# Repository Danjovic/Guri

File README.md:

# Guri
Ignition controller for VW air cooled engines.

Volkswagen air cooled engines have been produced over 70 years and millions of them still in use today pushing beetles, buses and even small aircraft. Such engines cheap and easy to maintain yet their outdated design provides space for a lot of hacking. 

The present project addresses a small but important improvement in the engine by the control of coil charging time and providing constant time for burning the fuel mixture allover the engine RPM range.

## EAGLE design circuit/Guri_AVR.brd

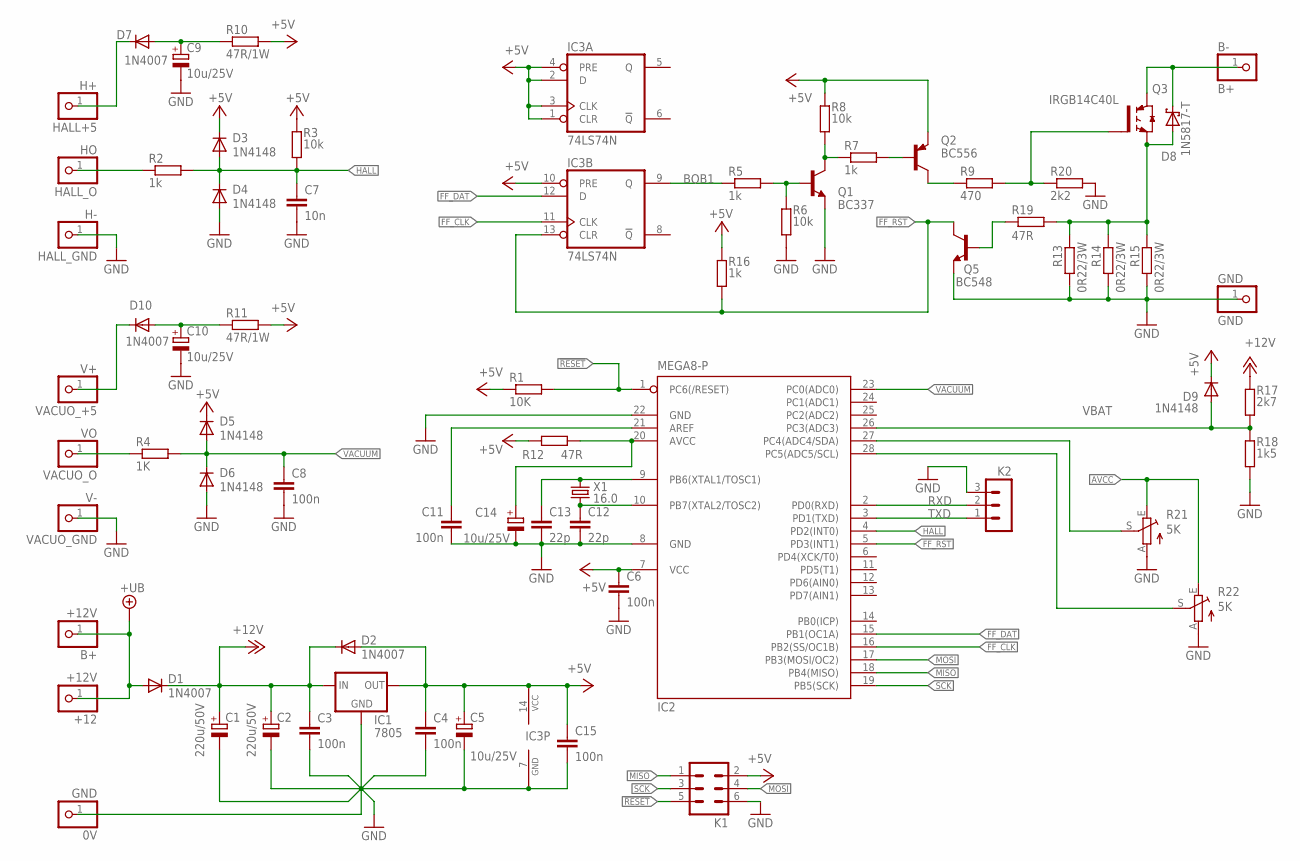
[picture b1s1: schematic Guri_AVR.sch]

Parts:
0V: GND; 1X01
+12: +12V; 1X01
B+: +12V; 1X01
B-: B+; 1X01
C1, C2: 220u/50V; E5-10,5
C3, C4, C6, C8, C11, C15: 100n; C050-025X075
C5, C9, C10, C14: 10u/25V; E2-5
C7: 10n; C050-025X075
C12, C13: 22p; C050-024X044
D1, D2, D7, D10: 1N4007; D-7.5
D3, D4, D5, D6, D9: 1N4148; DO35-7
D8: 1N5817-T; DO41-7.6
GND: GND; 1X01
H+: HALL+5; 1X01
H-: HALL_GND; 1X01
HO: HALL_O; 1X01
IC1: 7805; 78XXS
IC2: MEGA8-P; DIL28-3
IC3: 74LS74N; DIL14
K1: ML6
K2: MA03-1
Q1: BC337; TO92-EBC
Q2: BC556; TO92-EBC
Q3: IRGB14C40L; TO262-V
Q5: BC548; TO92-EBC
R1: 10K; 0207/7L
R2, R5, R7, R16: 1k; 0207/7L
R3, R6, R8: 10k; 0207/7L
R4: 1K; 0207/7L
R9: 470; 0207/7L
R10, R11: 47R/1W; 0207/7L
R12, R19: 47R; 0207/7L
R13, R14, R15: 0R22/3W; 0309/10
R17: 2k7; 0207/7L
R18: 1k5; 0207/7L
R20: 2k2; 0207/7L
R21, R22: 5K; ECP10P
V+: VACUO_+5; 1X01
V-: VACUO_GND; 1X01
VO: VACUO_O; 1X01
X1: 16.0; HC49/S

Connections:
!RESET: IC2.1 (PC6(/RESET)), K1.5, R1.4 (2)
+5V: C4.1, C5.+, C6.1, C15.1, D2.A, D3.C, D5.C, D9.C, IC1.OUT, IC2.7 (VCC), IC3.1 (CLR), IC3.2 (D), IC3.3 (CLK), IC3.4 (PRE), IC3.10 (PRE), IC3.14 (VCC), K1.2, Q2.E, R1.3 (1), R3.4 (2), R8.4 (2), R10.4 (2), R11.4 (2), R12.4 (2), R16.4 (2)
+12V: C1.+, C2.+, C3.1, D1.C, D2.C, IC1.IN, R17.3 (1)
+UB: +12.1, B+.1, D1.A
AREF: C11.1, IC2.21 (AREF)
AVCC: C14.+, IC2.20 (AVCC), R12.3 (1), R21.E, R22.E
BOB1: IC3.9 (Q), R5.3 (1)
FF_CLK: IC2.16 (PB2(SS/OC1B)), IC3.11 (CLK)
FF_DAT: IC2.15 (PB1(OC1A)), IC3.12 (D)
FF_RST: IC2.5 (PD3(INT1)), IC3.13 (CLR), Q5.C, R16.3 (1)
GND: 0V.1, C1.-, C2.-, C3.2, C4.2, C5.-, C6.2, C7.2, C8.2, C9.-, C10.-, C11.2, C12.2, C13.2, C14.-, C15.2, D4.A, D6.A, GND.1, H-.1, IC1.GND, IC2.8 (GND), IC2.22 (GND), IC3.7 (GND), K1.6, K2.3, Q1.E, Q5.E, R6.3 (1), R13.1, R14.1, R15.1, R18.4 (2), R20.4 (2), R21.A, R22.A, V-.1
HALL: C7.1, D3.A, D4.C, IC2.4 (PD2(INT0)), R2.4 (2), R3.3 (1)
HALL_IN: HO.1, R2.3 (1)
MISO: IC2.18 (PB4(MISO)), K1.1
MOSI: IC2.17 (PB3(MOSI/OC2)), K1.4
unnamed: C9.+, D7.A, R10.3 (1)
unnamed: D10.C, V+.1
unnamed: Q2.B, R7.4 (2)
unnamed: Q1.C, R7.3 (1), R8.3 (1)
unnamed: Q1.B, R5.4 (2), R6.4 (2)
unnamed: C10.+, D10.A, R11.3 (1)
unnamed: D7.C, H+.1
unnamed: Q2.C, R9.3 (1)
unnamed: Q3.1 (G), R9.4 (2), R20.3 (1)
unnamed: B-.1, D8.C, Q3.2 (C)
unnamed: C13.1, IC2.9 (PB6(XTAL1/TOSC1)), X1.2
unnamed: C12.1, IC2.10 (PB7(XTAL2/TOSC2)), X1.1
unnamed: Q5.B, R19.4 (2)
unnamed: IC2.27 (PC4(ADC4/SDA)), R21.S
unnamed: IC2.28 (PC5(ADC5/SCL)), R22.S
unnamed: D8.A, Q3.3 (E), R13.2, R14.2, R15.2, R19.3 (1)
RXD: IC2.2 (PD0(RXD)), K2.2
SCK: IC2.19 (PB5(SCK)), K1.3
TXD: IC2.3 (PD1(TXD)), K2.1
VAC-IN: R4.3 (1), VO.1
VACUUM: C8.1, D5.A, D6.C, IC2.23 (PC0(ADC0)), R4.4 (2)
VBAT: D9.A, IC2.26 (PC3(ADC3)), R17.4 (2), R18.3 (1)

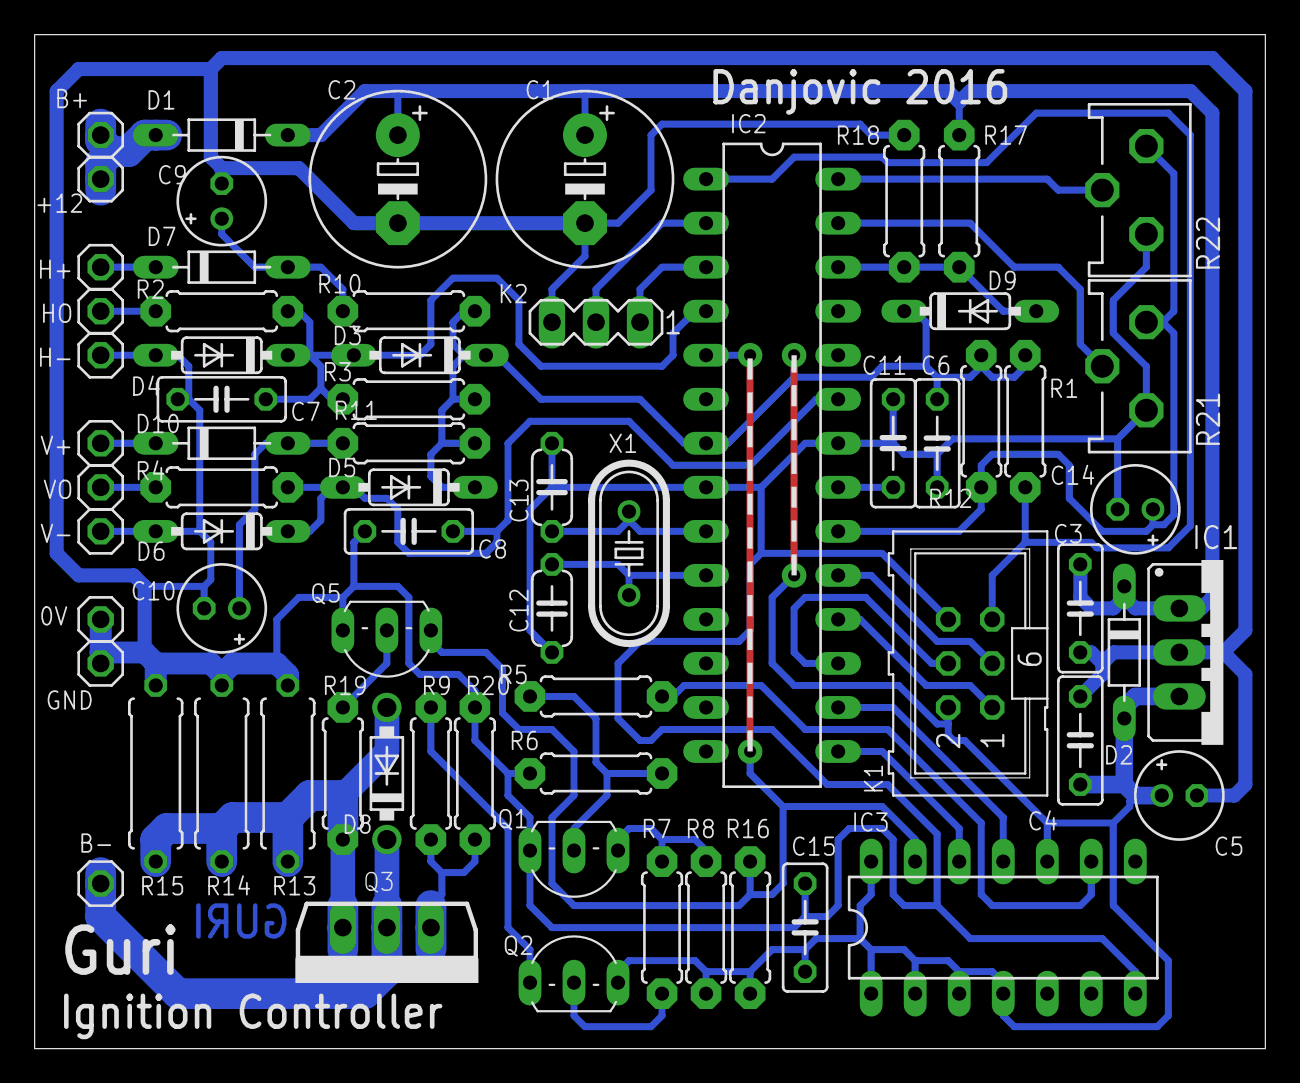
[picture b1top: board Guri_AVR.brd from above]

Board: 2 copper layers, 71.0 x 58.5 mm, 68 parts (0 on the bottom side), 37 nets.

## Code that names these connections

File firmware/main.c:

/*
   Guri: Ignition Timing Controller for VW Air Cooled engines
   
   Danjovic 2016 - Danjovic@hotmail.com
 

                    ATMega8
                   +---_---+  
        nRESET/PC6-|1    28|- PC5/ADC5/SCL - POT2
   DEBUG - RXD/PD0-|2    27|- PC4/ADC4/SDA - POT1
   DEBUG - TXD/PD1-|3    26|- PC3/ADC3 - VBAT
 IGNTSTS -INT0/PD2-|4    25|- PC2/ADC2
 OVERCUR  INT1/PD3-|5    24|- PC1/ADC1
        XCK\T0/PD4-|6    23|- PC0/ADC0 - VACUUM
               VCC-|7    22|- GND 
               GND-|8    21|- AREF
           XT1/PB6-|9    20|- AVCC
           XT2/PB7-|10   19|- PB5/SCK
            T1/PD5-|11   18|- PB4/MISO
          AIN0/PD6-|12   17|- PB3/MOSI/OC2
          AIN1/PD7-|13   16|- PB2/nSS/OC1B - FF_CLK
          ICP1/PB0-|14   15|- PB1/OC1A - FF_DAT
                   +-------+
   
*/

#define DEBUG

// *******************************Libraries************************
#include <avr/io.h>
#include <avr/pgmspace.h>
#include <avr/interrupt.h>
#include <inttypes.h>
#include <util/delay.h>
#include <avr/wdt.h> 

#ifdef DEBUG
#include <stdio.h>
#include "uart.h"
#include "uart.c"

#endif
// *******************************Definitions**********************
#define FF_CLK (1<<PB2)
#define FF_DAT (1<<PB1)

//


//F_CPU 12000000

#define TIME_FACTOR 64000000UL/F_CPU  // us
#define RPM_FACTOR  7500000UL
#define MIN_RPM      150
#define MAX_RPM     6200

#define _t_max_rpm  RPM_FACTOR/MAX_RPM     
#define _t_min_rpm  62500    //  120 RPM
#define _t_base     2000 / TIME_FACTOR // 2ms
#define _t_burn     500 / TIME_FACTOR  // 0,5ms 

#define _v_8V       114   // ADC reading for 8Volts
#define _v_15V      214   // ADC reading for 15Volts
#define _delta_Vbat ( _v_15V - _v_8V ) // delta


#define _v_127mmHg       114   // ADC reading for 127.5 mmHg
#define _v_270mmHg      214   // ADC reading for 270 mmHg
#define _delta_Vacuum ( _v_270mmHg - _v_127mmHg ) // delta


#define _v_factor      8    // Multiply factor to reduce loss of bits
                         // in the interpolation
#define _v_interval    15   // ending interval 


// *******************************Variables************************
static volatile uint8_t Vbat=0;
static volatile uint8_t Vacuum=0;


const uint16_t PROGMEM Tcharge[16] = { 600,575,550,525,500,475,450,425,400,375,350,325,300,275,250,225 };
const uint16_t PROGMEM Tvacuum[16] = {   0, 25, 50, 75,100,125,150,175,200,225,250,275,300,325,350,375 };
//const uint16_t PROGMEM constants[] = {_t_max_rpm, _t_min_rpm, _t_base, _t_burn } ;

// *******************************Function Prototypes**************
void init_hw(void);
uint16_t read_adc(uint8_t channel);


// *******************************Main Loop************************
int main (void) {

	uint8_t v;
	uint16_t temp16;

	init_hw();      // Initialize hardware
	                // Initialize variables
#ifdef DEBUG
	uart_init();    // Initialize USART, 19200 8N1
    stdout = &uart_output;
    stdin  = &uart_input;
	printf_P(PSTR("Guri:Debug mode\n"));
			   
#endif			   


    while(1) {
        puts("Press a Key");
        v = getchar();
		temp16=read_adc(0); printf("vacuum: %u\n",temp16);  
		temp16=read_adc(3); printf("vbat  : %u\n",temp16);  
		temp16=read_adc(4); printf("pot1  : %u\n",temp16);  
		temp16=read_adc(5); printf("pot2  : %u\n",temp16); 
 		
    }
		   
		   
			   
	//sei();     // start interrupts
	
	wdt_reset();
	wdt_disable();
	wdt_enable(WDTO_500MS);
	
	for (;;) {
		// reset watchdog
		wdt_reset();
		
		// read Vbat
		ADCSRA &= ~7; // select channel 0 (VBAT)
		ADCSRA |= ADSC; // start conversion
		while  	bit_is_set(ADCSRA, ADSC); // wait end of conversion
		v = ADCH; // read Battery voltage
		if (v < _v_8V ) v  =  _v_8V;  // low value limit
		if (v > _v_15V ) v = _v_15V;  // high value limit
		// convert value into index to lookup table		
		temp16 = (v - _v_8V) * ( _v_factor * _v_interval);
		temp16 = temp16 / (_v_factor * _delta_Vbat);
		v = (uint8_t)temp16;
		Vbat = v;
		
	
		// read Vaccum sensor
		ADCSRA |= 1; // select channel 1 (VACUUM)
		ADCSRA |= ADSC; // start conversion
		while  	bit_is_set(ADCSRA, ADSC); // wait end of conversion
		v = ADCH; // read vacuum at Manifold	
		if (v < _v_127mmHg ) v  =  _v_127mmHg;  // low value limit
		if (v > _v_270mmHg ) v = _v_270mmHg;  // high value limit
		// convert value into index to lookup table
		temp16 = (v - _v_127mmHg) * ( _v_factor * _v_interval);
		temp16 = temp16 / (_v_factor * _delta_Vacuum);
		v = (uint8_t)temp16;		
		Vacuum = v;
		
	}

}

// ******************************Initialize Hardware***************
void init_hw(void){
	
	// Initialize I/O
	DDRB = (FF_CLK | FF_DAT);
	PORTB = 0;
	PORTB |= FF_CLK;  // pulse clock to turn off coil 
	PORTB = 0;
	
	// Initialize ADC
	ADMUX =  (1<<REFS0); // Aref=AVcc
	ADCSRA=(1<<ADEN)|(1<<ADPS2)|(1<<ADPS1)|(1<<ADPS0); //Prescalar div factor =128
  
	
	// Initialize Timer
	TCCR1A=0;          // Timer 1 in Normal mode, OC1A/B disconnected
	TCNT1  = 0;        // Clear Timer1
	TCCR1B=(3<CS10);   // Prescaler 64, overflow 262ms
	
	// Initialize Interrupts
	TIMSK = (1<<TOIE1) + (1<<OCIE1A) + (1<<OCIE1B) ;// Overflow, compare A and B
	MCUCR = (3<<ISC01);// INT0 on rising edge
	GICR  = (1<<INT0); // INT0  
	//sei();
}

// ******************************Perform one Analog reading********
uint16_t read_adc(uint8_t channel) {
		ADMUX &= ~7;     //clear 3 lsb from channel selection
		ADMUX |= ( channel & 7); // range check in argument
		ADCSRA |= (1<<ADSC); // start conversion
		while  	bit_is_set(ADCSRA, ADSC); // wait end of conversion
		return ADC; // read Battery voltage, 8 bits
}

// ******************************Timer 1 Overflow******************
ISR (TIMER1_OVF_vect) {
	
	PORTB &= ~FF_DAT;   // Turn off coil and timers
	asm ("nop");		
	PORTB |= FF_CLK;
	asm ("nop");
	PORTB &= ~FF_CLK;
	
	TCCR1B = 0;           // Stop Timer1
	TCNT1  = 0;           // Clear Timer1
	
	TIMSK = (1<<TOIE1);	// Disable compare interrupts
}

// ******************************Timer 1 Compare A*****************
ISR (TIMER1_COMPA_vect) {     // Start Charging the Coil 
	PORTB |= FF_DAT;
	asm ("nop");	
	PORTB |= FF_CLK;
	asm ("nop");
	PORTB &= ~FF_CLK;
}

// ******************************Timer 1 Compare B*****************
ISR (TIMER1_COMPB_vect) {     // Stop Charge, generate Spark
	PORTB &= ~FF_DAT;
	asm ("nop");	
	PORTB |= FF_CLK;
	asm ("nop");
	PORTB &= ~FF_CLK;
}

// ******************************External Interrupt****************
ISR (INT0_vect) {             // Measure Tcycle
	uint16_t t_cycle=TCNT1;
	TCNT1=0;
	TCCR1B=(3<CS10);   // (re)start timer, Prescaler 64	
	
	PORTB &= ~FF_DAT;  // turn off coil if we reach here 
	asm ("nop");	   // before Compare B interrupt
	PORTB |= FF_CLK;
	asm ("nop");
	PORTB &= ~FF_CLK;
	
	
	// Check if RPM is valid. This function has a side effect of
	// limiting maximum RPM by not programming a spark either on 
	// too high or too low engine speeds
	if ((t_cycle > _t_max_rpm) && (t_cycle < _t_min_rpm) ) { 
	
		// compute spark time
		t_cycle -= _t_base ;                    // base time
		t_cycle -= pgm_read_word (&Tvacuum[Vacuum]); // vaccum advance time
		OCR1B = t_cycle;
		
		// compute Start of charge time but leave room for the mixture 
		// to burn. This may reduce coil charging time.
		t_cycle -= pgm_read_word(&Tcharge[Vbat]);  // compute charge time
		if (t_cycle < _t_burn) t_cycle = _t_burn; // leave room
		OCR1A = t_cycle;
		
		// (re)program compare interrupts
		TIMSK = (1<<TOIE1) + (1<<OCIE1A) + (1<<OCIE1B) ;
		
	} else { 
		// Disable compare interrupts
		TIMSK = (1<<TOIE1);
	}	

}

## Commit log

2016-04-18 Preliminary schematic & PCB
    Preliminary schematic and printed circuit board
2016-04-22 New layout for preliminary board
2016-04-27 Main function for the signal generator
2016-04-27 organizing of file tree
